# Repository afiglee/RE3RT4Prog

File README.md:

Firmware is located at https://github.com/afiglee/PROMProgrammer
Version 1 which is as of Aug 21, 2024 should work

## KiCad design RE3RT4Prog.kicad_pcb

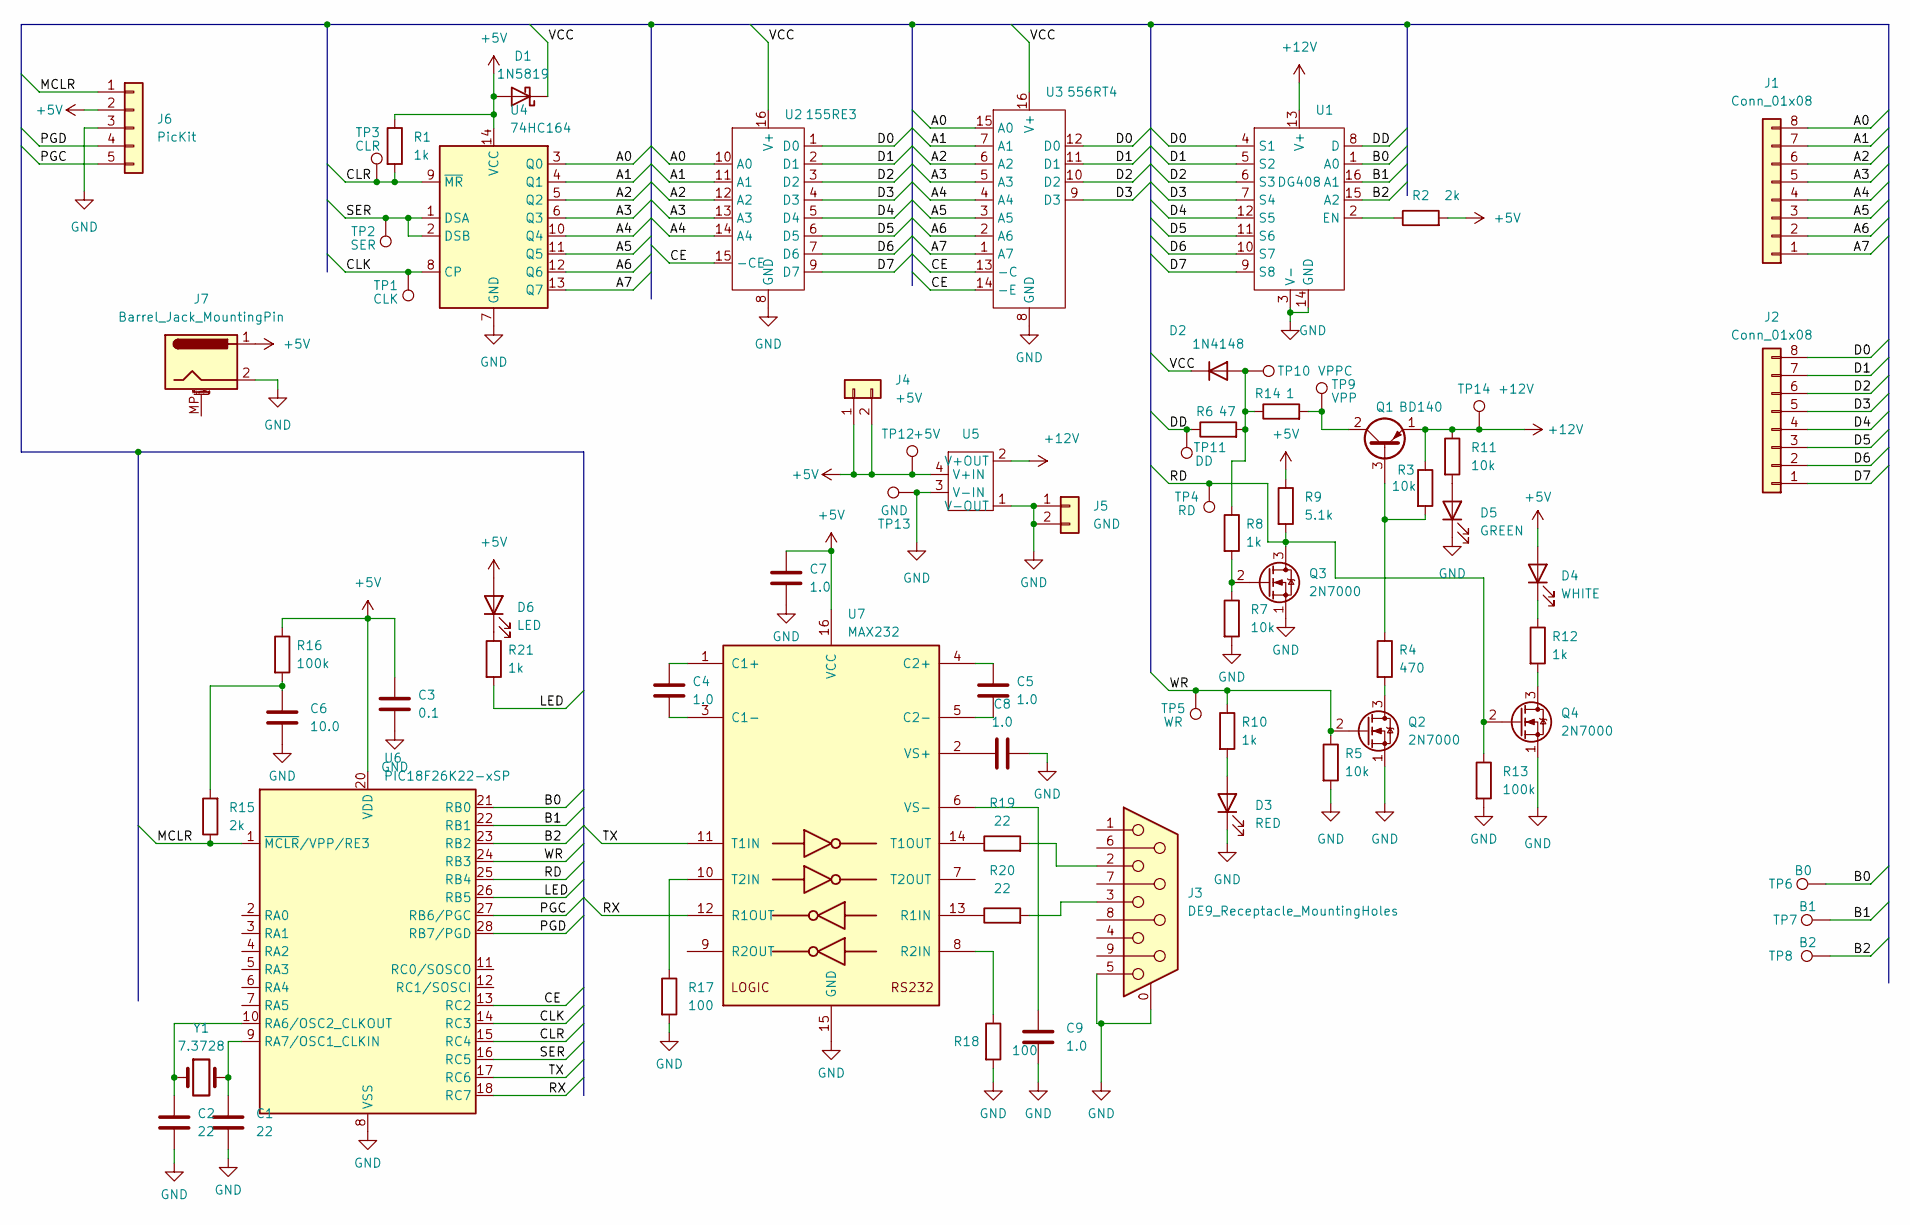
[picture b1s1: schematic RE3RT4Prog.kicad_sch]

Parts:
C1, C2: 22; C_Disc_D3.4mm_W2.1mm_P2.50mm
C3: 0.1; C_0603_1608Metric_Pad1.08x0.95mm_HandSolder
C4, C5, C7, C8, C9: 1.0; C_Disc_D4.3mm_W1.9mm_P5.00mm
C6: 10.0; C_Disc_D4.3mm_W1.9mm_P5.00mm
D1: 1N5819; D_DO-41_SOD81_P10.16mm_Horizontal
D2: 1N4148; D_DO-35_SOD27_P7.62mm_Horizontal
D3: RED; LED_D5.0mm
D4: WHITE; LED_D5.0mm
D5: GREEN; LED_D5.0mm
D6: LED; LED_D5.0mm
J1, J2: Conn_01x08; PinHeader_1x08_P2.54mm_Vertical
J3: DE9_Receptacle_MountingHoles; DSUB-9_Female_Horizontal_P2.77x2.84mm_EdgePinOffset4.94mm_H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
J4: +5V; PinHeader_1x02_P2.54mm_Vertical
J5: GND; PinHeader_1x02_P2.54mm_Vertical
J6: PicKit; PinHeader_1x05_P2.54mm_Vertical
J7: Barrel_Jack_MountingPin; BarrelJack_GCT_DCJ200-10-A_Horizontal
Q1: BD140; TO-126-3_Vertical
Q2, Q3, Q4: 2N7000; TO-92_Inline
R1, R8, R10, R12, R21: 1k; R_Axial_DIN0207_L6.3mm_D2.5mm_P10.16mm_Horizontal
R2, R15: 2k; R_Axial_DIN0207_L6.3mm_D2.5mm_P10.16mm_Horizontal
R3, R5, R7, R11: 10k; R_Axial_DIN0207_L6.3mm_D2.5mm_P10.16mm_Horizontal
R4: 470; R_Axial_DIN0207_L6.3mm_D2.5mm_P10.16mm_Horizontal
R6: 47; R_Axial_DIN0207_L6.3mm_D2.5mm_P10.16mm_Horizontal
R9: 5.1k; R_Axial_DIN0207_L6.3mm_D2.5mm_P10.16mm_Horizontal
R13, R16: 100k; R_Axial_DIN0207_L6.3mm_D2.5mm_P10.16mm_Horizontal
R14: 1; R_Axial_DIN0207_L6.3mm_D2.5mm_P10.16mm_Horizontal
R17, R18: 100; R_Axial_DIN0207_L6.3mm_D2.5mm_P10.16mm_Horizontal
R19, R20: 22; R_Axial_DIN0207_L6.3mm_D2.5mm_P10.16mm_Horizontal
TP1: CLK; TestPoint_Loop_D3.50mm_Drill0.9mm_Beaded
TP2: SER; TestPoint_Loop_D3.50mm_Drill0.9mm_Beaded
TP3: CLR; TestPoint_Loop_D3.50mm_Drill0.9mm_Beaded
TP4: RD; TestPoint_Loop_D3.50mm_Drill0.9mm_Beaded
TP5: WR; TestPoint_Loop_D3.50mm_Drill0.9mm_Beaded
TP6: B0; TestPoint_Loop_D3.50mm_Drill0.9mm_Beaded
TP7: B1; TestPoint_Loop_D3.50mm_Drill0.9mm_Beaded
TP8: B2; TestPoint_Loop_D3.50mm_Drill0.9mm_Beaded
TP9: VPP; TestPoint_Loop_D3.50mm_Drill0.9mm_Beaded
TP10: VPPC; TestPoint_Loop_D3.50mm_Drill0.9mm_Beaded
TP11: DD; TestPoint_Loop_D3.50mm_Drill0.9mm_Beaded
TP12: +5V; TestPoint_Loop_D3.50mm_Drill0.9mm_Beaded
TP13: GND; TestPoint_Loop_D3.50mm_Drill0.9mm_Beaded
TP14: +12V; TestPoint_Loop_D3.50mm_Drill0.9mm_Beaded
U1: DG408; DIP-16_W7.62mm_Socket_LongPads
U2: 155RE3; DIP_Socket-16_W4.3_W5.08_W7.62_W10.16_W10.9_3M_216-3340-00-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
U3: 556RT4; DIP_Socket-16_W4.3_W5.08_W7.62_W10.16_W10.9_3M_216-3340-00-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
U4: 74HC164; DIP-14_W7.62mm_Socket_LongPads
U5: MT3608
U6: PIC18F26K22-xSP; DIP-28_W7.62mm_Socket_LongPads
U7: MAX232; DIP-16_W7.62mm_Socket_LongPads
Y1: 7.3728; Crystal_HC49-U_Vertical

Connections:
+5V: C3.1, C7.1, D1.2 (A), D4.2 (A), D6.2 (A), J4.1, J4.2, J6.2, J7.1, R1.1, R2.2, R9.1, R16.1, TP12.1, U4.14 (VCC), U5.4 (V+IN), U6.20 (VDD), U7.16 (VCC)
+12V: Q1.1 (E), R3.1, R11.1, TP14.1, U1.13 (V+), U5.2 (V+OUT)
/A0: J1.8, U2.10 (A0), U3.15 (A0), U4.3 (Q0)
/A1: J1.7, U2.11 (A1), U3.7 (A1), U4.4 (Q1)
/A2: J1.6, U2.12 (A2), U3.6 (A2), U4.5 (Q2)
/A3: J1.5, U2.13 (A3), U3.5 (A3), U4.6 (Q3)
/A4: J1.4, U2.14 (A4), U3.4 (A4), U4.10 (Q4)
/A5: J1.3, U3.3 (A5), U4.11 (Q5)
/A6: J1.2, U3.2 (A6), U4.12 (Q6)
/A7: J1.1, U3.1 (A7), U4.13 (Q7)
/B0: TP6.1, U1.1 (A0), U6.21 (RB0)
/B1: TP7.1, U1.16 (A1), U6.22 (RB1)
/B2: TP8.1, U1.15 (A2), U6.23 (RB2)
/CE: U2.15 (-CE), U3.13 (-C), U3.14 (-E), U6.13 (RC2)
/CLK: TP1.1, U4.8 (CP), U6.14 (RC3)
/CLR: R1.2, TP3.1, U4.9 (~MR), U6.15 (RC4)
/D0: J2.8, U1.4 (S1), U2.1 (D0), U3.12 (D0)
/D1: J2.7, U1.5 (S2), U2.2 (D1), U3.11 (D1)
/D2: J2.6, U1.6 (S3), U2.3 (D2), U3.10 (D2)
/D3: J2.5, U1.7 (S4), U2.4 (D3), U3.9 (D3)
/D4: J2.4, U1.12 (S5), U2.5 (D4)
/D5: J2.3, U1.11 (S6), U2.6 (D5)
/D6: J2.2, U1.10 (S7), U2.7 (D6)
/D7: J2.1, U1.9 (S8), U2.9 (D7)
/DD: R6.1, TP11.1, U1.8 (D)
/LED: R21.2, U6.26 (RB5)
/MCLR: J6.1, R15.1, U6.1 (~MCLR/VPP/RE3)
/PGC: J6.5, U6.27 (RB6/PGC)
/PGD: J6.4, U6.28 (RB7/PGD)
/RD: Q3.3 (D), Q4.2 (G), R9.2, R13.1, TP4.1, U6.25 (RB4)
/RX: U6.18 (RC7), U7.12 (R1OUT)
/SER: TP2.1, U4.1 (DSA), U4.2 (DSB), U6.16 (RC5)
/TX: U6.17 (RC6), U7.11 (T1IN)
/VCC: D1.1 (K), D2.1 (K), U2.16 (V+), U3.16 (V+)
/WR: Q2.2 (G), R5.1, R10.1, TP5.1, U6.24 (RB3)
GND: C1.2, C2.2, C3.2, C6.2, C7.2, C8.2, C9.2, D3.1 (K), D5.1 (K), J3.0 (PAD), J3.5, J5.1, J5.2, J6.3, J7.2, Q2.1 (S), Q3.1 (S), Q4.1 (S), R5.2, R7.2, R13.2, R17.2, R18.2, TP13.1, U1.3 (V-), U1.14 (GND), U2.8 (GND), U3.8 (GND), U4.7 (GND), U5.1 (V-OUT), U5.3 (V-IN), U6.8 (VSS), U6.19 (VSS), U7.15 (GND)
unnamed: C6.1, R15.2, R16.2
unnamed: D2.2 (A), R6.2, R8.1, R14.1, TP10.1
unnamed: D3.2 (A), R10.2
unnamed: D4.1 (K), R12.1
unnamed: D5.2 (A), R11.2
unnamed: D6.1 (K), R21.1
unnamed: J3.2, R19.2
unnamed: J3.3, R20.2
unnamed: Q1.3 (B), R3.2, R4.1
unnamed: Q1.2 (C), R14.2, TP9.1
unnamed: Q2.3 (D), R4.2
unnamed: Q3.2 (G), R7.1, R8.2
unnamed: Q4.3 (D), R12.2
unnamed: R2.1, U1.2 (EN)
unnamed: C2.1, U6.10 (RA6/OSC2_CLKOUT), Y1.1
unnamed: C1.1, U6.9 (RA7/OSC1_CLKIN), Y1.2
unnamed: C4.1, U7.1 (C1+)
unnamed: C4.2, U7.3 (C1-)
unnamed: C5.1, U7.4 (C2+)
unnamed: C5.2, U7.5 (C2-)
unnamed: R20.1, U7.13 (R1IN)
unnamed: R18.1, U7.8 (R2IN)
unnamed: R19.1, U7.14 (T1OUT)
unnamed: R17.1, U7.10 (T2IN)
unnamed: C8.1, U7.2 (VS+)
unnamed: C9.1, U7.6 (VS-)

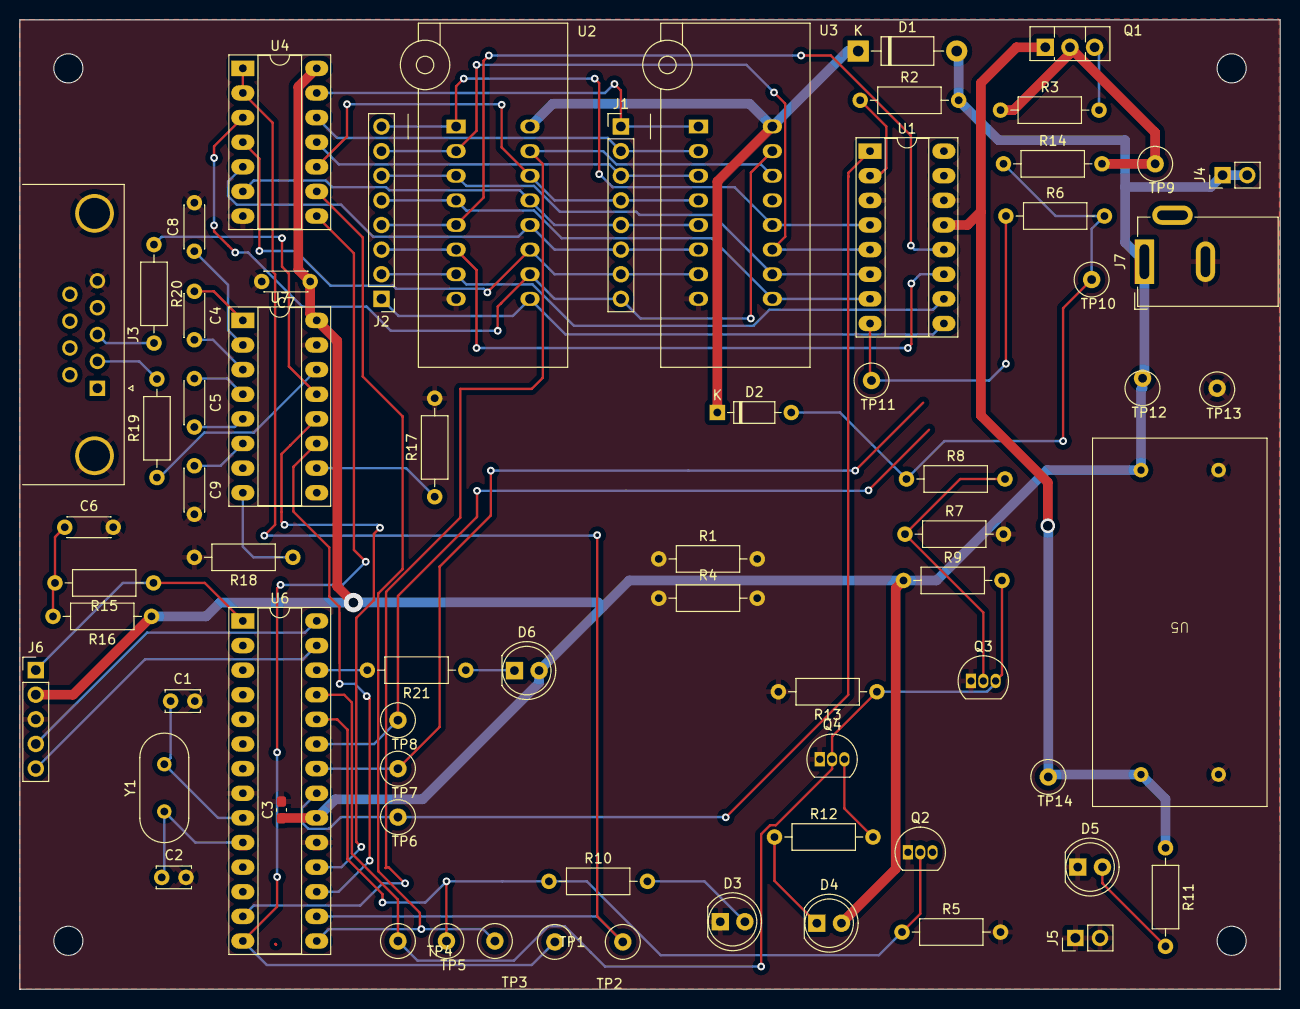
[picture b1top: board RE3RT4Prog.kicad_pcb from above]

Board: 2 copper layers, 130.0 x 100.0 mm, 69 parts (0 on the bottom side), 62 nets.

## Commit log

2024-06-27 Schema almost done
2024-06-27 Schema done with fottprints
2024-06-28 Work in progress
2024-07-03 Work in progress, close
2024-08-21 Works with RT4 and RE3, but PCB needs to be updated
2024-12-30 Added AVRISP connector
